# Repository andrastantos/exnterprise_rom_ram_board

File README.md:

A 512kB RAM and ROM expansion design for the Enterprise computer
===================================================================

This design can be used to add up to 512kB of ROM as well as 512kB of RAM without using up any external connectors of the computer.
It can also be used (by populating the ROM socket with a second RAM chip) to add 1MB of RAM to the machine.

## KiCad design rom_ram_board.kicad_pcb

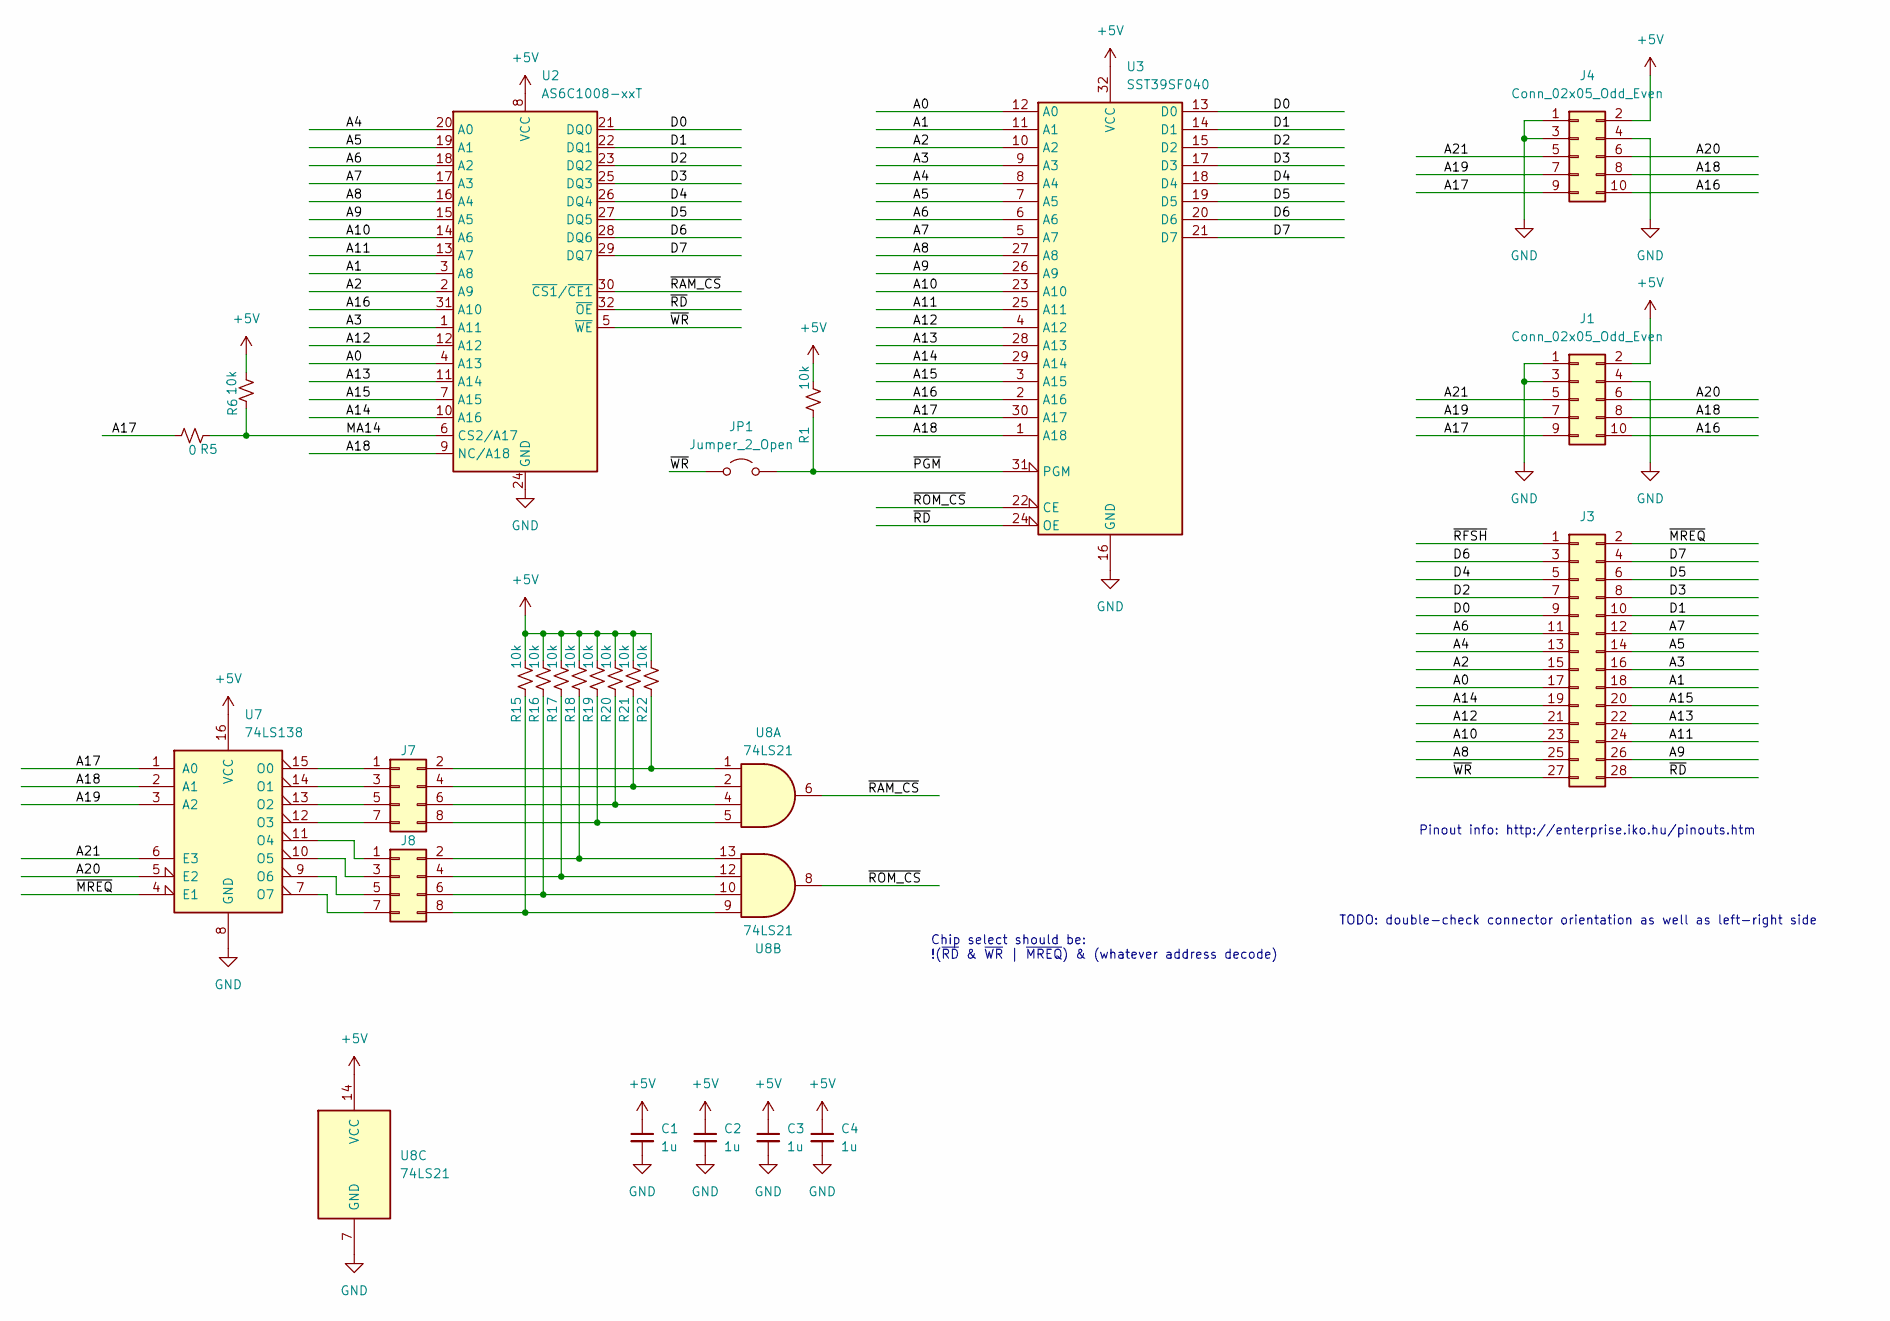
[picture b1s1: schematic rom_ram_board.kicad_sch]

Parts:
C1, C2, C3, C4: 1u; C_0603_1608Metric_Pad1.08x0.95mm_HandSolder
J1: Conn_02x05_Odd_Even; PinHeader_2x05_P2.54mm_Vertical
J3: Conn_02x16_Row_Letter_First; PinSocket_2x14_P2.54mm_Vertical
J4: Conn_02x05_Odd_Even; PinSocket_2x05_P2.54mm_Vertical
J7, J8: Conn_02x02_Odd_Even; PinHeader_2x04_P2.54mm_Vertical
JP1: Jumper_2_Open; PinHeader_1x02_P2.54mm_Vertical
R1, R6, R15, R16, R17, R18, R19, R20, R21, R22: 10k; R_0603_1608Metric_Pad0.98x0.95mm_HandSolder
R5: 0; R_0603_1608Metric_Pad0.98x0.95mm_HandSolder
U2: AS6C1008-xxT; TSOP-I-32_11-18.4x8mm_P0.5mm
U3: SST39SF040; DIP-32_W15.24mm_Socket_LongPads
U7: 74LS138; SO-16_3.9x9.9mm_P1.27mm
U8: 74LS21; SO-14_3.9x8.65mm_P1.27mm

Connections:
+5V: C1.1, C2.1, C3.1, C4.1, J1.2, J4.2, R1.1, R6.1, R15.1, R16.1, R17.1, R18.1, R19.1, R20.1, R21.1, R22.1, U2.8 (VCC), U3.32 (VCC), U7.16 (VCC), U8.14 (VCC)
/A0: J3.17, U2.4 (A13), U3.12 (A0)
/A1: J3.18, U2.3 (A8), U3.11 (A1)
/A2: J3.15, U2.2 (A9), U3.10 (A2)
/A3: J3.16, U2.1 (A11), U3.9 (A3)
/A4: J3.13, U2.20 (A0), U3.8 (A4)
/A5: J3.14, U2.19 (A1), U3.7 (A5)
/A6: J3.11, U2.18 (A2), U3.6 (A6)
/A7: J3.12, U2.17 (A3), U3.5 (A7)
/A8: J3.25, U2.16 (A4), U3.27 (A8)
/A9: J3.26, U2.15 (A5), U3.26 (A9)
/A10: J3.23, U2.14 (A6), U3.23 (A10)
/A11: J3.24, U2.13 (A7), U3.25 (A11)
/A12: J3.21, U2.12 (A12), U3.4 (A12)
/A13: J3.22, U2.11 (A14), U3.28 (A13)
/A14: J3.19, U2.10 (A16), U3.29 (A14)
/A15: J3.20, U2.7 (A15), U3.3 (A15)
/A16: J1.10, J4.10, U2.31 (A10), U3.2 (A16)
/A17: J1.9, J4.9, R5.1, U3.30 (A17), U7.1 (A0)
/A18: J1.8, J4.8, U2.9 (NC/A18), U3.1 (A18), U7.2 (A1)
/A19: J1.7, J4.7, U7.3 (A2)
/A20: J1.6, J4.6, U7.5 (E2)
/A21: J1.5, J4.5, U7.6 (E3)
/D0: J3.9, U2.21 (DQ0), U3.13 (D0)
/D1: J3.10, U2.22 (DQ1), U3.14 (D1)
/D2: J3.7, U2.23 (DQ2), U3.15 (D2)
/D3: J3.8, U2.25 (DQ3), U3.17 (D3)
/D4: J3.5, U2.26 (DQ4), U3.18 (D4)
/D5: J3.6, U2.27 (DQ5), U3.19 (D5)
/D6: J3.3, U2.28 (DQ6), U3.20 (D6)
/D7: J3.4, U2.29 (DQ7), U3.21 (D7)
/MA14: R5.2, R6.2, U2.6 (CS2/A17)
/~MREQ: J3.2, U7.4 (E1)
/~PGM: JP1.2 (B), R1.2, U3.31 (PGM)
/~RAM_CS: U2.30 (~CS1/~CE1), U8.6
/~RD: J3.28, U2.32 (~OE), U3.24 (OE)
/~RFSH: J3.1
/~ROM_CS: U3.22 (CE), U8.8
/~WR: J3.27, JP1.1 (A), U2.5 (~WE)
GND: C1.2, C2.2, C3.2, C4.2, J1.1, J1.3, J1.4, J4.1, J4.3, J4.4, U2.24 (GND), U3.16 (GND), U7.8 (GND), U8.7 (GND)
unnamed: J7.1, U7.15 (O0)
unnamed: J7.2, R22.2, U8.1
unnamed: J7.3, U7.14 (O1)
unnamed: J7.4, R21.2, U8.2
unnamed: J7.5, U7.13 (O2)
unnamed: J7.6, R20.2, U8.4
unnamed: J7.7, U7.12 (O3)
unnamed: J7.8, R19.2, U8.5
unnamed: J8.1, U7.11 (O4)
unnamed: J8.2, R18.2, U8.13
unnamed: J8.3, U7.10 (O5)
unnamed: J8.4, R17.2, U8.12
unnamed: J8.5, U7.9 (O6)
unnamed: J8.6, R16.2, U8.10
unnamed: J8.7, U7.7 (O7)
unnamed: J8.8, R15.2, U8.9

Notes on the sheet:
TODO: double-check connector orientation as well as left-right side
Pinout info: http://enterprise.iko.hu/pinouts.htm
Chip select should be: !(~{RD} & ~{WR} | ~{MREQ}) & (whatever address decode)

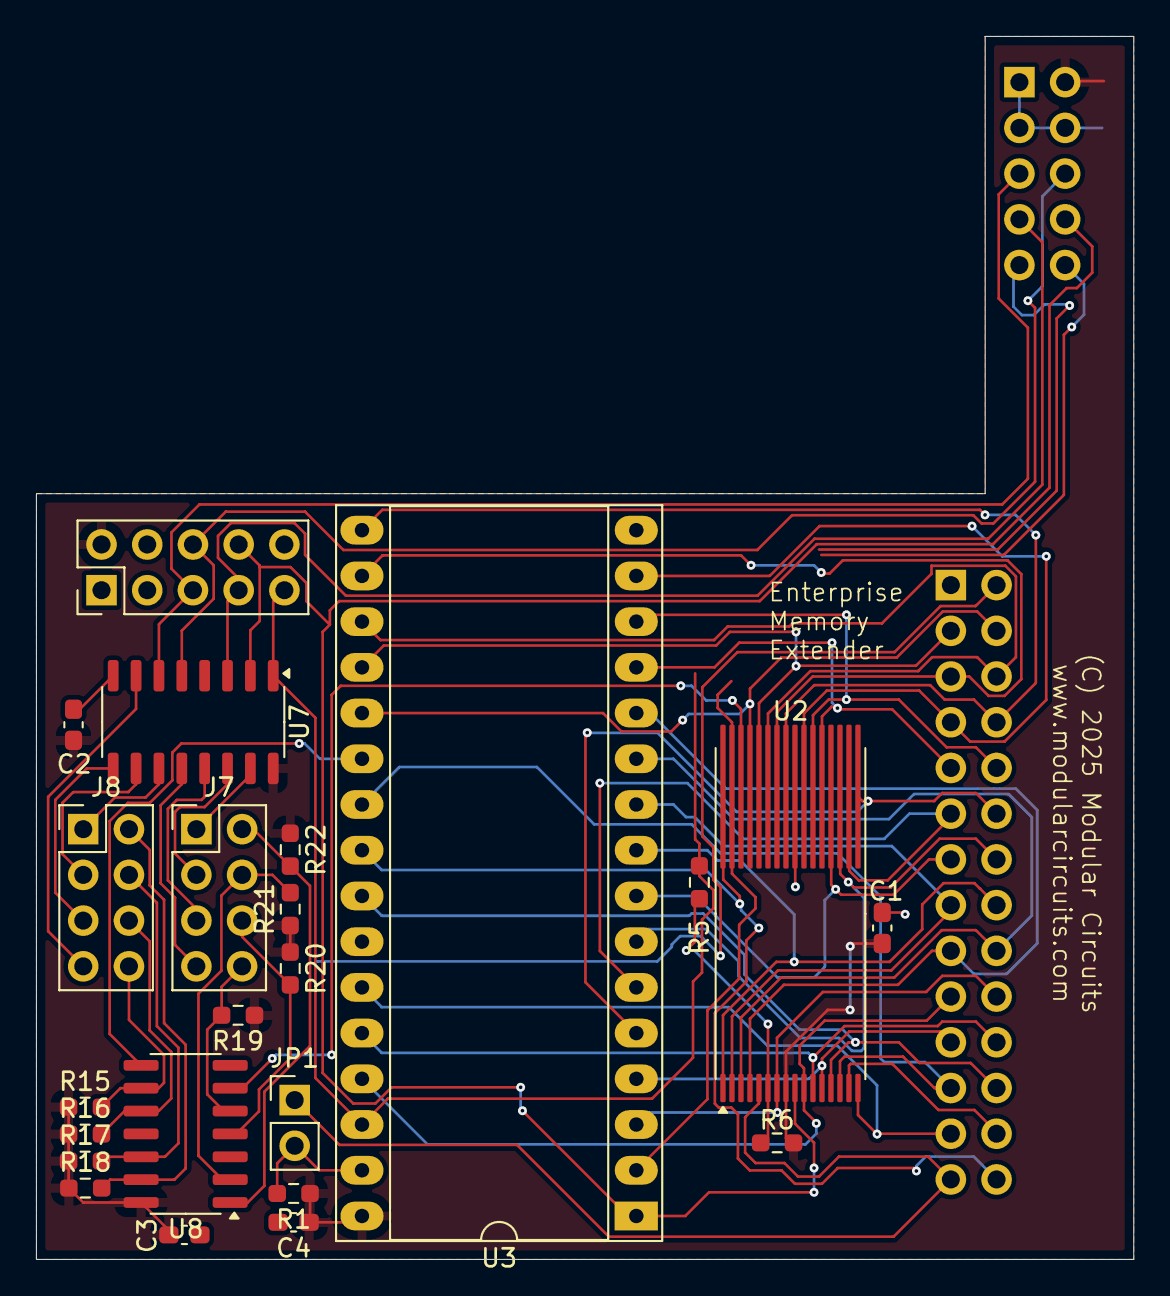
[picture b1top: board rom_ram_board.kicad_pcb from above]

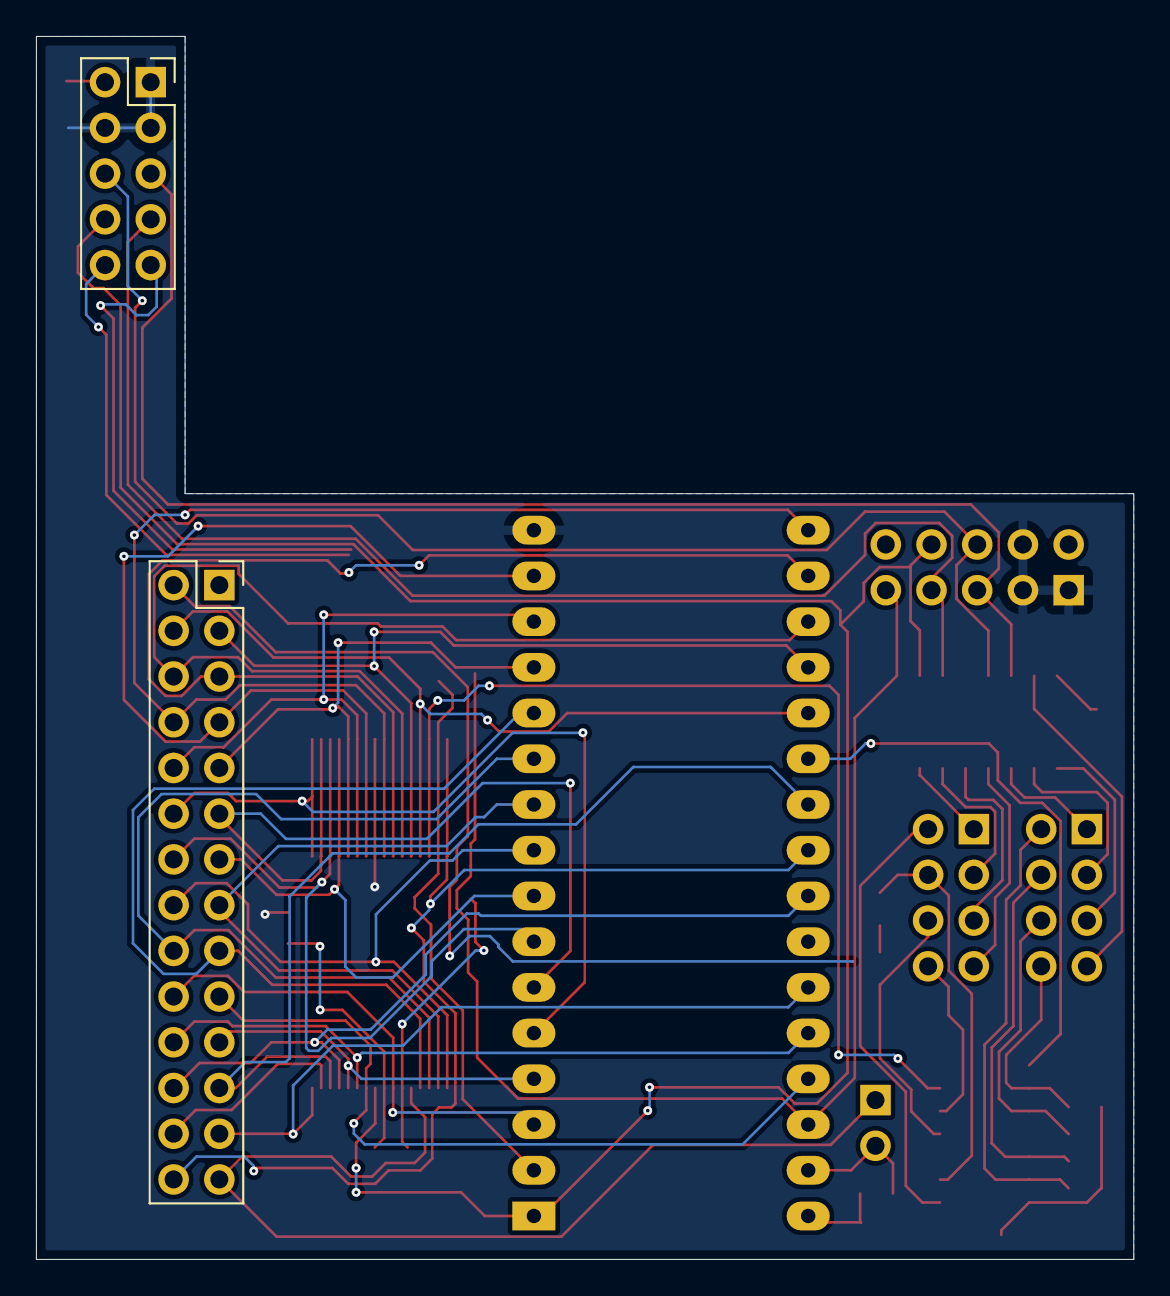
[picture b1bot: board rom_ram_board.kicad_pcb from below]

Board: 2 copper layers, 61.0 x 67.9 mm, 25 parts (2 on the bottom side), 55 nets.

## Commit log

2025-02-17 Incomplete design, checking in for tracking only.
2025-02-17 A very short project description.
2025-02-25 Another README update.
2025-02-25 Another README update

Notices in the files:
rom_ram_board.kicad_pcb:
(C) 2025 Modular Circuits
